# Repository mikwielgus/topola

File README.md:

<!--
SPDX-FileCopyrightText: 2024 Topola contributors

SPDX-License-Identifier: MIT
-->

# Topola

[Topola](https://topola.dev) is a work-in-progress interactive
topological router for printed circuit boards (PCBs) in Rust.

## Chat

Join the official [Matrix
chatroom](https://matrix.to/#/%23topola:tchncs.de) or [IRC
channel](https://webchat.oftc.net/?channels=#topola) to talk with the
developers. Both chatrooms are bridged, so it does not matter which one
you join.

## Installation

To install Topola, follow our [Installation guide](INSTALL.md).

## Contributing

*Anyone* can contribute to Topola, including you. If you want to help us out,
follow our [Contribution guide](CONTRIBUTING.md).

The easiest way to contribute is by reporting issues on our
[issue tracker](https://codeberg.org/topola/topola/issues). If you know any
language other than English, you can help by translating Topola on
[Codeberg's Weblate](https://translate.codeberg.org/engage/topola/).

Our official repository is on
[Codeberg](https://codeberg.org/topola/topola). We also have a mirror
repository on [GitHub](https://github.com/mikwielgus/topola).

## Licence

Topola is licensed under the [MIT licence](LICENSES/MIT.txt). Files present in
the `assets/` directory are dual-licensed as under MIT or
[Creative Commons Attribution 4.0 International](LICENSES/CC-BY-4.0.txt)
licence. The file `crates/planar-incr-embed/src/math.rs` is dual-licensed as under
MIT or [Apache 2.0](LICENSES/Apache-2.0.txt) licence.

### Inbound licence is outbound licence

Unless you explicitly state otherwise, any contribution intentionally submitted
for inclusion in the work by you will be licensed as described above, without
any additional terms or conditions.

## Acknowledgements

This project is funded through the NGI0 Entrust Fund, a fund established by
NLnet with financial support from the European Commission's Next Generation
Internet programme, under the aegis of DG Communications Networks, Content and
Technology under grant agreement No 101069594.

## Gallery

![Screenshot of a PCB layout of an IR remote with a 3x4 tactswitch keyboard,
displayed in KiCad.](./assets/screenshots/3x4_tactswitch_ir_remote.png "3x4 tactswitch IR remote PCB layout in KiCad")

![Screenshot of a PCB layout of a THT DB-25 to THT DB-25 gender changer adapter
board, displayed in KiCad](./assets/screenshots/tht_db25_to_tht_db25.png "THT DB-25 to THT DB-25 gender changer adapter PCB layout in KiCad")

![Screenshot of a PCB layout of a 4x4 1206 LED matrix breakout board, displayed
in KiCad](./assets/screenshots/4x4_1206_led_matrix_breakout.png "4x4 1206 LED matrix breakout PCB layout in KiCad")

![Animation. There is a rubber band-like trace following cursor,
navigating a very simple maze. The maze and the trace are red, the
background is solid black but also very slightly white and dark
blue.](./assets/screencasts/pre-egui_interactive_routing.gif "Interactive routing")

![Animation showing a trace, behaving like a rubber band, routed around
obstacles step by step. Attempted alternative paths and a guiding mesh
are shown.](./assets/screencasts/pre-egui_debug_visualization.gif "Debug visualization")

![Animation. There are two upward barriers, with some space between tem,
around which four rubberband traces, one over another, are wrapped.
Enter mouse cursor. The cursor begins to stretch the left barrier to the
right. As it's stretched, the traces cease to be wrapped around the
right barrier, becoming "free". The traces and the barrier are
two-dimensional and all solid red. The background is black but also very
slightly white and blue.](./assets/screencasts/pre-egui_unwrapping_bends.gif "Unwrapping bends")

![This animation shows four traces wrapped around a vertical barrier
like rubberbands. Computer cursor appears and starts dragging the
barrier's top end left and right, up and down, elastically stretching
the barrier and having the traces continue being wrapped on the barrier
regardless of its position. The traces and the barrier are all solid
red. The background is black but also very slightly white and
blue.](./assets/screencasts/pre-egui_dragging_with_bends.gif "Dragging with bends")

![Animation. There is an upward barrier in the middle and dots on the
left and right of it, four each. A trace is drawn from the leftmost dot
on the left to the rightmost dot on the right. Then a trace is drawn
from the second leftmost dot on the left to the second rightmost dot on
the right, displacing the previous trace so that there's space for the
new one. Same happens for the remaining dots. The dots, traces and
barrier are all solid red. The background is black but also very
slightly white and blue.](./assets/screencasts/pre-egui_squeezing_through_under_bends.gif "Squeezing through under bends")

![Animation showing three red-colored traces pass around a barrier.
Trace bends are not aligned to a grid unlike most PCB layouts these days
(this is called "topological routing"). The traces and the barrier are
all solid red. The background is black but also very slightly white and
blue.](./assets/screenshots/pre-egui_stacked_bends.png "Stacking bends")

![Animation showing a trace zigzagging around two barriers. The trace
and the barriers are all solid red. The background is black but also
very slightly white and blue.](./assets/screenshots/pre-egui_zigzag.png "Zigzag")

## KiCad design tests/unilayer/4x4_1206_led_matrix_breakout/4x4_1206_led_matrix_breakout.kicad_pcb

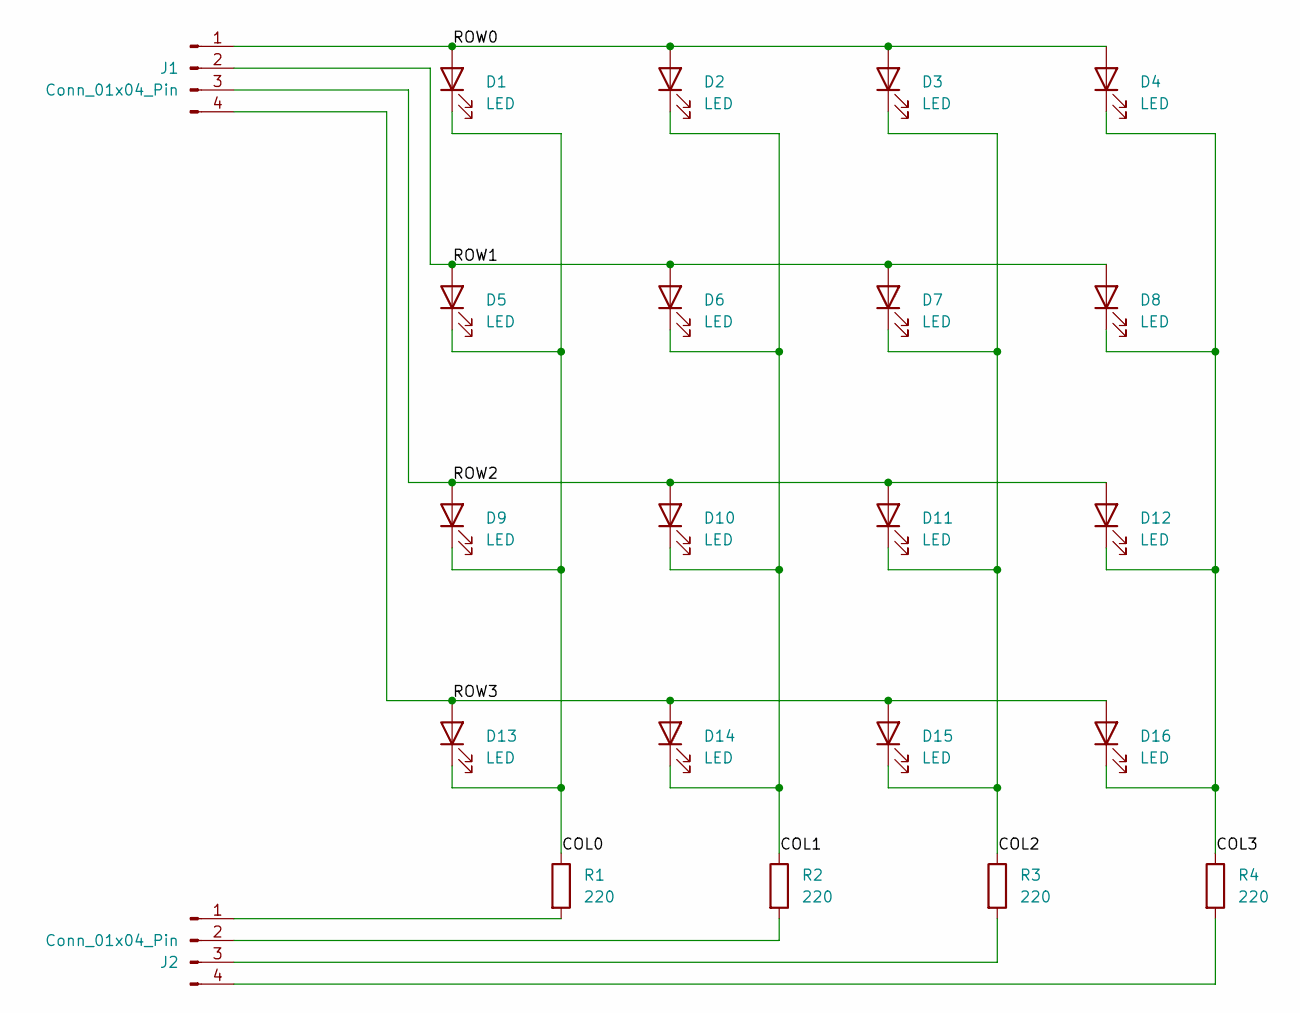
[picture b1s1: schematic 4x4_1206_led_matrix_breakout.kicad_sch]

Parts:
D1, D2, D3, D4, D5, D6, D7, D8, D9, D10, D11, D12, D13, D14, D15, D16: LED; LED_1206_3216Metric
J1, J2: Conn_01x04_Pin; PinHeader_1x04_P2.54mm_Horizontal
R1, R2, R3, R4: 220; R_0603_1608Metric

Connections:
/COL0: D1.1 (K), D5.1 (K), D9.1 (K), D13.1 (K), R1.1
/COL1: D2.1 (K), D6.1 (K), D10.1 (K), D14.1 (K), R2.1
/COL2: D3.1 (K), D7.1 (K), D11.1 (K), D15.1 (K), R3.1
/COL3: D4.1 (K), D8.1 (K), D12.1 (K), D16.1 (K), R4.1
/ROW0: D1.2 (A), D2.2 (A), D3.2 (A), D4.2 (A), J1.1
/ROW1: D5.2 (A), D6.2 (A), D7.2 (A), D8.2 (A), J1.2
/ROW2: D9.2 (A), D10.2 (A), D11.2 (A), D12.2 (A), J1.3
/ROW3: D13.2 (A), D14.2 (A), D15.2 (A), D16.2 (A), J1.4
unnamed: J2.1, R1.2
unnamed: J2.2, R2.2
unnamed: J2.3, R3.2
unnamed: J2.4, R4.2

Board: 2 copper layers, 22 parts (2 on the bottom side), 12 nets, no tracks yet.

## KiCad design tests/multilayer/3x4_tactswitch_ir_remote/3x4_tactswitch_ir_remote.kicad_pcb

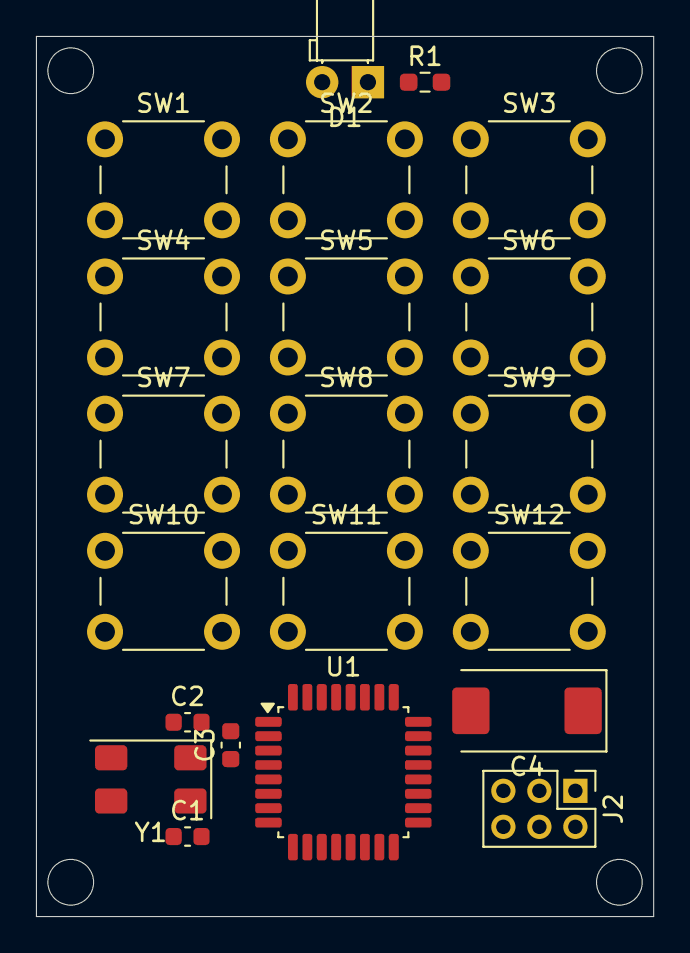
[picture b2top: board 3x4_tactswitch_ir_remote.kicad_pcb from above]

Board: 2 copper layers, 34.3 x 48.9 mm, 21 parts (0 on the bottom side), 17 nets, no tracks yet.

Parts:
C1, C2: 22p; C_0603_1608Metric
C3: 100n; C_0603_1608Metric
C4: 470u; CP_EIA-7343-31_Kemet-D
D1: IR204A; LED_D3.0mm_Horizontal_O1.27mm_Z2.0mm_IRBlack
J2: Conn_01x06_Pin; PinHeader_2x03_P2.00mm_Vertical
R1: 220; R_0603_1608Metric_Pad0.98x0.95mm_HandSolder
SW1, SW2, SW3, SW4, SW5, SW6, SW7, SW8, SW9, SW10, SW11, SW12: SW_Push; SW_PUSH_6mm
U1: ATmega328P-AU; TQFP-32_7x7mm_P0.8mm
Y1: Crystal_GND23; Crystal_SMD_0603-4Pin_6.0x3.5mm

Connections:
+5V: C3.1, C4.1, J2.1, U1.4 (VCC), U1.6 (VCC), U1.18 (AVCC), U1.20 (AREF)
/COL0: SW1.2, SW4.2, SW7.2, SW10.2, U1.12 (PB0)
/COL1: SW2.2, SW5.2, SW8.2, SW11.2, U1.13 (PB1)
/COL2: SW3.2, SW6.2, SW9.2, SW12.2, U1.14 (PB2)
/MISO: J2.4, U1.16 (PB4)
/MOSI: J2.3, U1.15 (PB3)
/RESET: J2.2, U1.29 (~RESET/PC6)
/ROW0: SW1.1, SW2.1, SW3.1, U1.23 (PC0)
/ROW1: SW4.1, SW5.1, SW6.1, U1.24 (PC1)
/ROW2: SW7.1, SW8.1, SW9.1, U1.25 (PC2)
/ROW3: SW10.1, SW11.1, SW12.1, U1.26 (PC3)
/SCK: J2.5, U1.17 (PB5)
GND: C1.1, C2.1, C3.2, C4.2, J2.6, R1.2, U1.3 (GND), U1.5 (GND), U1.21 (GND), Y1.2, Y1.3
unnamed: D1.2 (A), U1.30 (PD0)
unnamed: D1.1 (K), R1.1
unnamed: C2.2, U1.7 (XTAL1/PB6), Y1.1
unnamed: C1.2, U1.8 (XTAL2/PB7), Y1.4

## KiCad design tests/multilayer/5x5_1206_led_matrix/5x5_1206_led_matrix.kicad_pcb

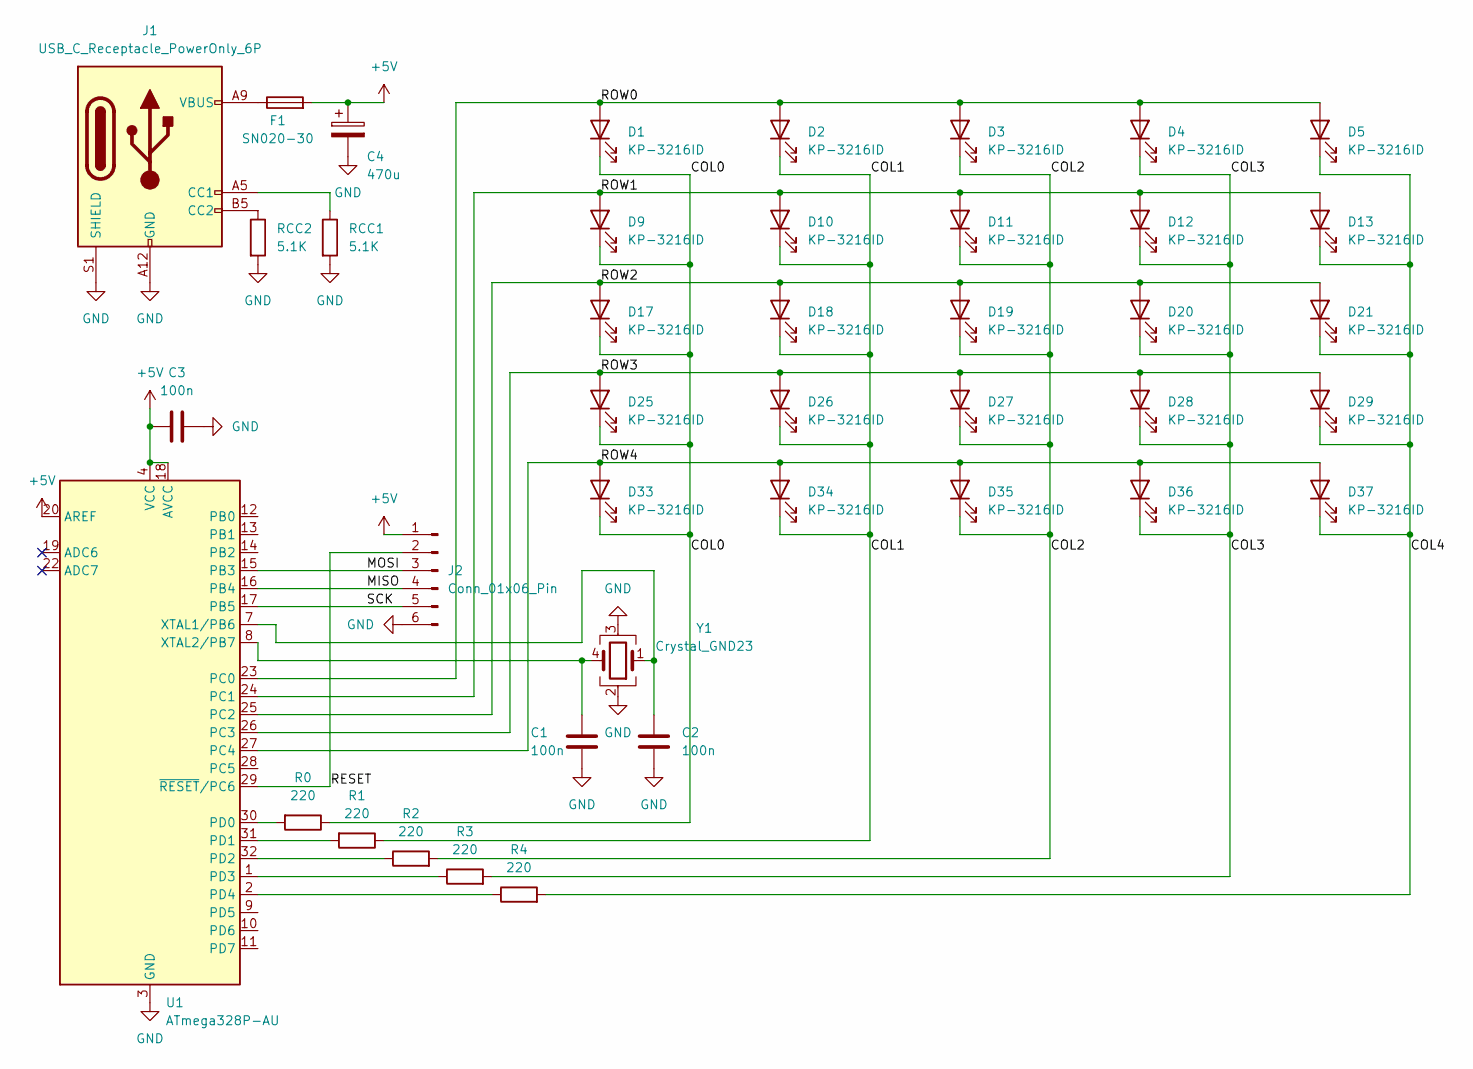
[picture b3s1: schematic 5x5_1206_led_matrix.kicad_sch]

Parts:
C1, C2, C3: 100n; C_0603_1608Metric
C4: 470u; CP_EIA-7343-31_Kemet-D
D1, D2, D3, D4, D5, D9, D10, D11, D12, D13, D17, D18, D19, D20, D21, D25, D26, D27, D28, D29, D33, D34, D35, D36, D37: KP-3216ID; LED_1206_3216Metric
F1: SN020-30; Fuse_1206_3216Metric
J1: USB_C_Receptacle_PowerOnly_6P; USB_C_Receptacle_GCT_USB4125-xx-x-0190_6P_TopMnt_Horizontal
J2: Conn_01x06_Pin; PinHeader_2x03_P2.00mm_Vertical
R0, R1, R2, R3, R4: 220; R_0603_1608Metric
RCC1, RCC2: 5.1K; R_0603_1608Metric
U1: ATmega328P-AU; TQFP-32_7x7mm_P0.8mm
Y1: Crystal_GND23; Crystal_SMD_0603-4Pin_6.0x3.5mm

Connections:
+5V: C3.1, C4.1, F1.2, J2.1, U1.4 (VCC), U1.6 (VCC), U1.18 (AVCC), U1.20 (AREF)
/COL0: D1.1 (K), D9.1 (K), D17.1 (K), D25.1 (K), D33.1 (K), R0.1
/COL1: D2.1 (K), D10.1 (K), D18.1 (K), D26.1 (K), D34.1 (K), R1.1
/COL2: D3.1 (K), D11.1 (K), D19.1 (K), D27.1 (K), D35.1 (K), R2.2
/COL3: D4.1 (K), D12.1 (K), D20.1 (K), D28.1 (K), D36.1 (K), R3.2
/COL4: D5.1 (K), D13.1 (K), D21.1 (K), D29.1 (K), D37.1 (K), R4.2
/MISO: J2.4, U1.16 (PB4)
/MOSI: J2.3, U1.15 (PB3)
/RESET: J2.2, U1.29 (~RESET/PC6)
/ROW0: D1.2 (A), D2.2 (A), D3.2 (A), D4.2 (A), D5.2 (A), U1.23 (PC0)
/ROW1: D9.2 (A), D10.2 (A), D11.2 (A), D12.2 (A), D13.2 (A), U1.24 (PC1)
/ROW2: D17.2 (A), D18.2 (A), D19.2 (A), D20.2 (A), D21.2 (A), U1.25 (PC2)
/ROW3: D25.2 (A), D26.2 (A), D27.2 (A), D28.2 (A), D29.2 (A), U1.26 (PC3)
/ROW4: D33.2 (A), D34.2 (A), D35.2 (A), D36.2 (A), D37.2 (A), U1.27 (PC4)
/SCK: J2.5, U1.17 (PB5)
GND: C1.1, C2.1, C3.2, C4.2, J1.A12 (GND), J1.B12 (GND), J1.S1 (SHIELD), J2.6, RCC1.2, RCC2.2, U1.3 (GND), U1.5 (GND), U1.21 (GND), U1.33 (GND), Y1.2, Y1.3
unnamed: F1.1, J1.A9 (VBUS), J1.B9 (VBUS)
unnamed: J1.A5 (CC1), RCC1.1
unnamed: J1.B5 (CC2), RCC2.1
unnamed: R0.2, U1.30 (PD0)
unnamed: R1.2, U1.31 (PD1)
unnamed: R2.1, U1.32 (PD2)
unnamed: R3.1, U1.1 (PD3)
unnamed: R4.1, U1.2 (PD4)
unnamed: C2.2, U1.7 (XTAL1/PB6), Y1.1
unnamed: C1.2, U1.8 (XTAL2/PB7), Y1.4

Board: 2 copper layers, 41 parts (16 on the bottom side), 26 nets, no tracks yet.

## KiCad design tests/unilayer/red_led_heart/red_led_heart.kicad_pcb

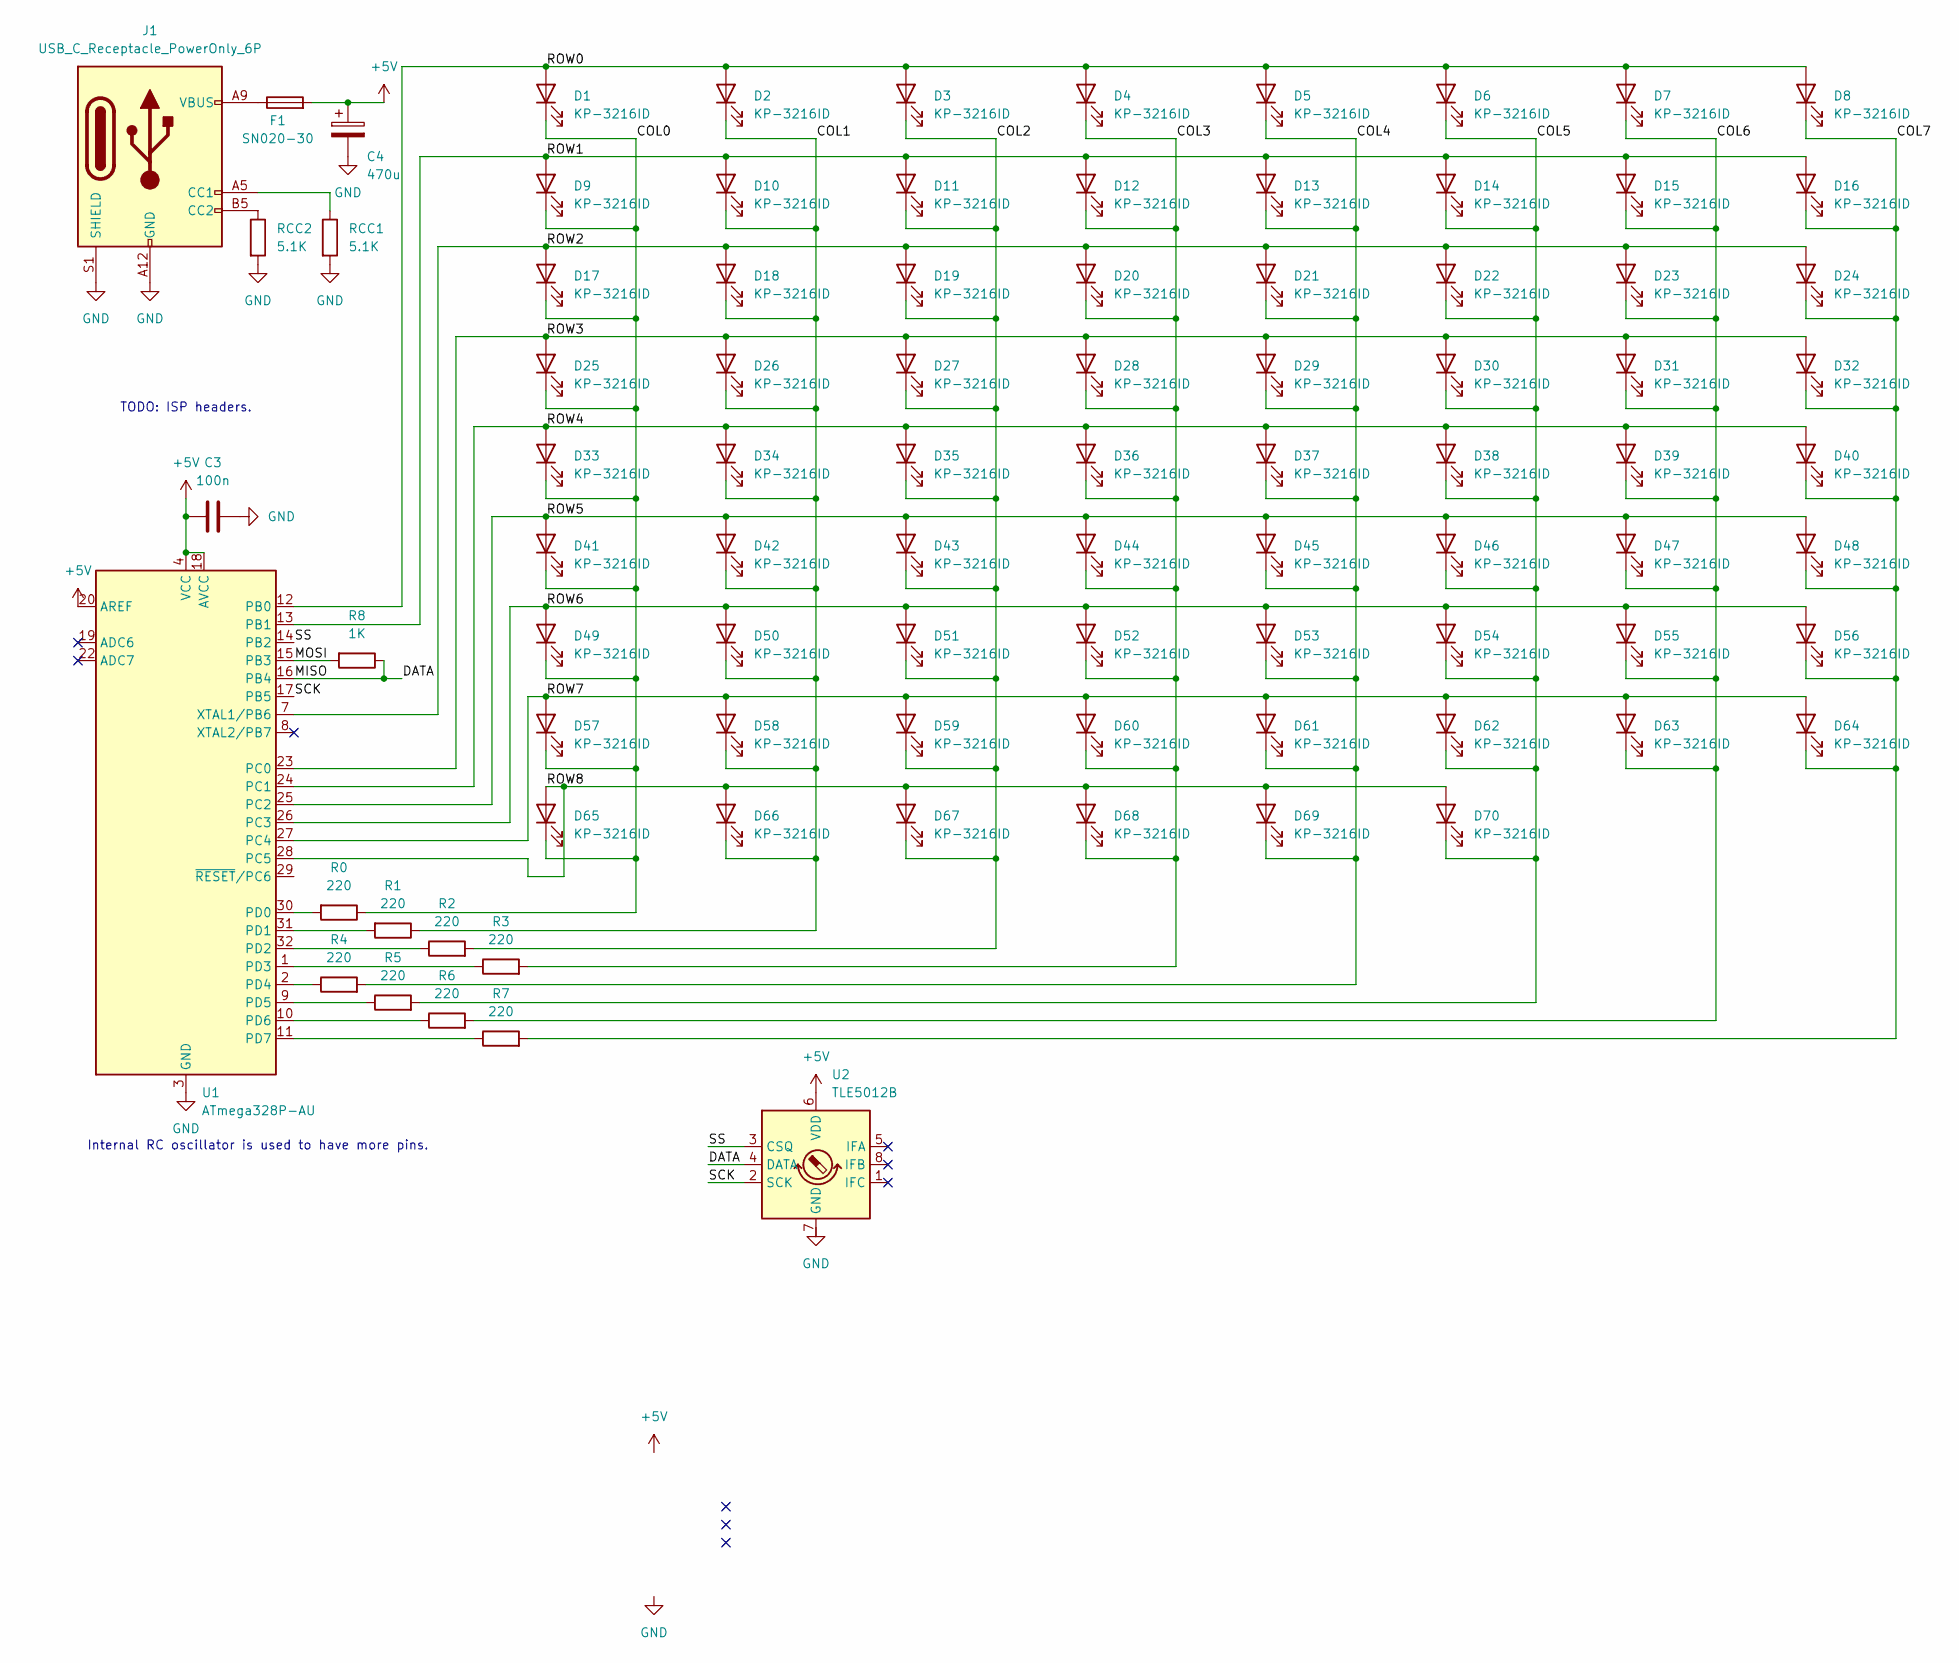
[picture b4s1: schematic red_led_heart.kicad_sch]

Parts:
C3: 100n; C_0603_1608Metric
C4: 470u; CP_EIA-7343-31_Kemet-D
D1, D2, D3, D4, D5, D6, D7, D8, D9, D10, D11, D12, D13, D14, D15, D16, D17, D18, D19, D20, D21, D22, D23, D24, D25, D26, D27, D28, D29, D30, D31, D32, D33, D34, D35, D36, D37, D38, D39, D40, D41, D42, D43, D44, D45, D46, D47, D48, D49, D50, D51, D52, D53, D54, D55, D56, D57, D58, D59, D60, D61, D62, D63, D64, D65, D66, D67, D68, D69, D70: KP-3216ID; LED_1206_3216Metric
F1: SN020-30; Fuse_1206_3216Metric
J1: USB_C_Receptacle_PowerOnly_6P; USB_C_Receptacle_GCT_USB4125-xx-x-0190_6P_TopMnt_Horizontal
R0, R1, R2, R3, R4, R5, R6, R7: 220; R_0603_1608Metric
R8: 1K; R_0603_1608Metric
RCC1, RCC2: 5.1K; R_0603_1608Metric
U1: ATmega328P-AU; TQFP-32_7x7mm_P0.8mm
U2: TLE5012B; SOIC-8_3.9x4.9mm_P1.27mm

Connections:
+5V: C3.1, C4.1, F1.2, U1.4 (VCC), U1.6 (VCC), U1.18 (AVCC), U1.20 (AREF), U2.6 (VDD)
/COL0: D1.1 (K), D9.1 (K), D17.1 (K), D25.1 (K), D33.1 (K), D41.1 (K), D49.1 (K), D57.1 (K), D65.1 (K), R0.1
/COL1: D2.1 (K), D10.1 (K), D18.1 (K), D26.1 (K), D34.1 (K), D42.1 (K), D50.1 (K), D58.1 (K), D66.1 (K), R1.1
/COL2: D3.1 (K), D11.1 (K), D19.1 (K), D27.1 (K), D35.1 (K), D43.1 (K), D51.1 (K), D59.1 (K), D67.1 (K), R2.2
/COL3: D4.1 (K), D12.1 (K), D20.1 (K), D28.1 (K), D36.1 (K), D44.1 (K), D52.1 (K), D60.1 (K), D68.1 (K), R3.2
/COL4: D5.1 (K), D13.1 (K), D21.1 (K), D29.1 (K), D37.1 (K), D45.1 (K), D53.1 (K), D61.1 (K), D69.1 (K), R4.2
/COL5: D6.1 (K), D14.1 (K), D22.1 (K), D30.1 (K), D38.1 (K), D46.1 (K), D54.1 (K), D62.1 (K), D70.1 (K), R5.2
/COL6: D7.1 (K), D15.1 (K), D23.1 (K), D31.1 (K), D39.1 (K), D47.1 (K), D55.1 (K), D63.1 (K), R6.2
/COL7: D8.1 (K), D16.1 (K), D24.1 (K), D32.1 (K), D40.1 (K), D48.1 (K), D56.1 (K), D64.1 (K), R7.2
/DATA: R8.1, U1.16 (PB4), U2.4 (DATA)
/MOSI: R8.2, U1.15 (PB3)
/ROW0: D1.2 (A), D2.2 (A), D3.2 (A), D4.2 (A), D5.2 (A), D6.2 (A), D7.2 (A), D8.2 (A), U1.12 (PB0)
/ROW1: D9.2 (A), D10.2 (A), D11.2 (A), D12.2 (A), D13.2 (A), D14.2 (A), D15.2 (A), D16.2 (A), U1.13 (PB1)
/ROW2: D17.2 (A), D18.2 (A), D19.2 (A), D20.2 (A), D21.2 (A), D22.2 (A), D23.2 (A), D24.2 (A), U1.7 (XTAL1/PB6)
/ROW3: D25.2 (A), D26.2 (A), D27.2 (A), D28.2 (A), D29.2 (A), D30.2 (A), D31.2 (A), D32.2 (A), U1.23 (PC0)
/ROW4: D33.2 (A), D34.2 (A), D35.2 (A), D36.2 (A), D37.2 (A), D38.2 (A), D39.2 (A), D40.2 (A), U1.24 (PC1)
/ROW5: D41.2 (A), D42.2 (A), D43.2 (A), D44.2 (A), D45.2 (A), D46.2 (A), D47.2 (A), D48.2 (A), U1.25 (PC2)
/ROW6: D49.2 (A), D50.2 (A), D51.2 (A), D52.2 (A), D53.2 (A), D54.2 (A), D55.2 (A), D56.2 (A), U1.26 (PC3)
/ROW7: D57.2 (A), D58.2 (A), D59.2 (A), D60.2 (A), D61.2 (A), D62.2 (A), D63.2 (A), D64.2 (A), U1.27 (PC4)
/ROW8: D65.2 (A), D66.2 (A), D67.2 (A), D68.2 (A), D69.2 (A), D70.2 (A), U1.28 (PC5)
/SCK: U1.17 (PB5), U2.2 (SCK)
/SS: U1.14 (PB2), U2.3 (CSQ)
GND: C3.2, C4.2, J1.A12 (GND), J1.B12 (GND), J1.S1 (SHIELD), RCC1.2, RCC2.2, U1.3 (GND), U1.5 (GND), U1.21 (GND), U1.33 (GND)
unnamed: F1.1, J1.A9 (VBUS), J1.B9 (VBUS)
unnamed: J1.A5 (CC1), RCC1.1
unnamed: J1.B5 (CC2), RCC2.1
unnamed: R0.2, U1.30 (PD0)
unnamed: R1.2, U1.31 (PD1)
unnamed: R2.1, U1.32 (PD2)
unnamed: R3.1, U1.1 (PD3)
unnamed: R4.1, U1.2 (PD4)
unnamed: R5.1, U1.9 (PD5)
unnamed: R6.1, U1.10 (PD6)
unnamed: R7.1, U1.11 (PD7)

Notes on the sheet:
Internal RC oscillator is used to have more pins.
TODO: ISP headers.

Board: 2 copper layers, 87 parts (17 on the bottom side), 34 nets, no tracks yet.

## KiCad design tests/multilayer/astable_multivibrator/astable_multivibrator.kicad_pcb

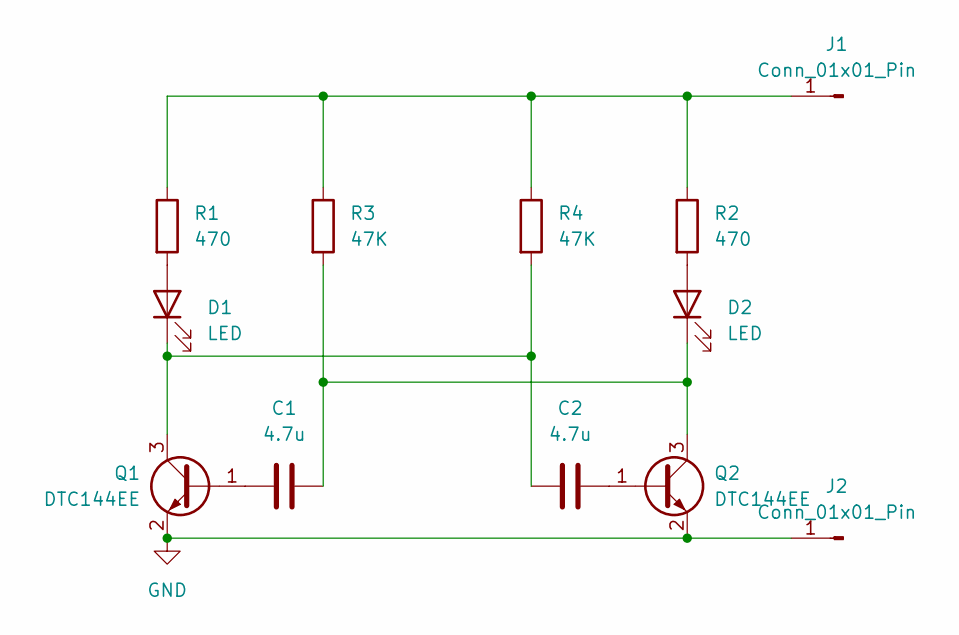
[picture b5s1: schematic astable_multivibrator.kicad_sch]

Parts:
C1, C2: 4.7u; C_0201_0603Metric
D1, D2: LED; LED_1206_3216Metric
J1, J2: Conn_01x01_Pin; SolderWire-0.1sqmm_1x01_D0.4mm_OD1mm
Q1, Q2: DTC144EE; SOT-523
R1, R2: 470; R_0201_0603Metric
R3, R4: 47K; R_0201_0603Metric

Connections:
GND: J2.1, Q1.2 (E), Q2.2 (E)
unnamed: D1.2 (A), R1.2
unnamed: C2.1, D1.1 (K), Q1.3 (C), R4.2
unnamed: D2.2 (A), R2.2
unnamed: C1.2, D2.1 (K), Q2.3 (C), R3.2
unnamed: J1.1, R1.1, R2.1, R3.1, R4.1
unnamed: C1.1, Q1.1 (B)
unnamed: C2.2, Q2.1 (B)

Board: 2 copper layers, 12 parts (10 on the bottom side), 8 nets, no tracks yet.

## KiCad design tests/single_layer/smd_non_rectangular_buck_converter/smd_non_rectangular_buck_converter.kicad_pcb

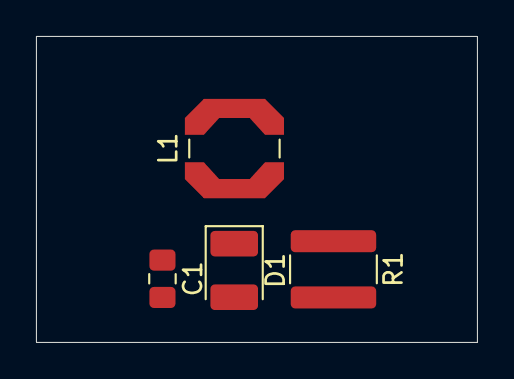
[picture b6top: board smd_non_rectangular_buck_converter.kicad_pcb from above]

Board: 2 copper layers, 24.5 x 17.0 mm, 4 parts (0 on the bottom side), 3 nets, no tracks yet.

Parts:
C1: C; C_0805_2012Metric_Pad1.18x1.45mm_HandSolder
D1: D; D_1210_3225Metric_Pad1.42x2.65mm_HandSolder
L1: L; L_Coilcraft_LPS5030
R1: R; R_1218_3246Metric_Pad1.22x4.75mm_HandSolder

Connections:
+3.3V: C1.1, L1.2, R1.1
GND: C1.2, D1.2 (A), R1.2
unnamed: D1.1 (K), L1.1

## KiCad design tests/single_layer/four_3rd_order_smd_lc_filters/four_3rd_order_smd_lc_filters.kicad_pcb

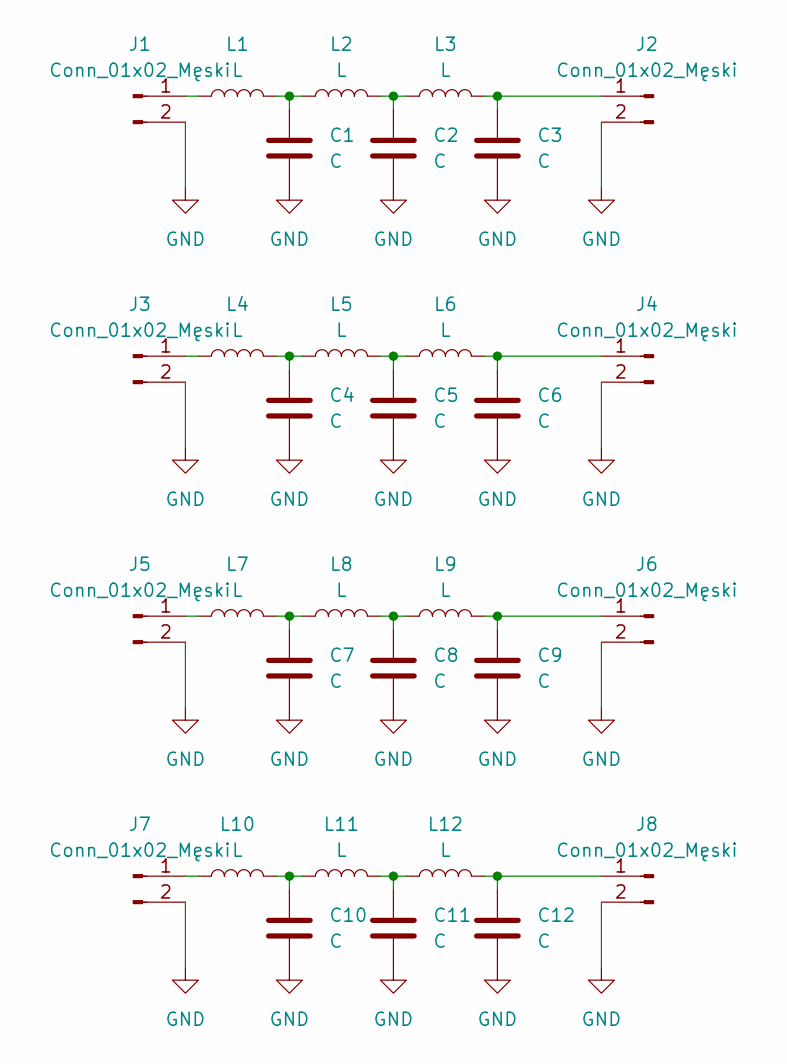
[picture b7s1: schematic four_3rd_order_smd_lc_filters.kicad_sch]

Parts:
C1, C2, C3, C4, C5, C6, C7, C8, C9, C10, C11, C12: C; C_0603_1608Metric_Pad1.08x0.95mm_HandSolder
J1, J2, J3, J4, J5, J6, J7, J8: Conn_01x02_Męski; PinHeader_1x02_P1.00mm_Horizontal
L1, L2, L3, L4, L5, L6, L7, L8, L9, L10, L11, L12: L; L_0603_1608Metric_Pad1.05x0.95mm_HandSolder

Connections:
GND: C1.2, C2.2, C3.2, C4.2, C5.2, C6.2, C7.2, C8.2, C9.2, C10.2, C11.2, C12.2, J1.2, J2.2, J3.2, J4.2, J5.2, J6.2, J7.2, J8.2
unnamed: C1.1, L1.2, L2.1
unnamed: C2.1, L2.2, L3.1
unnamed: C4.1, L4.2, L5.1
unnamed: C5.1, L5.2, L6.1
unnamed: C7.1, L7.2, L8.1
unnamed: C8.1, L8.2, L9.1
unnamed: C10.1, L10.2, L11.1
unnamed: C11.1, L11.2, L12.1
unnamed: J1.1, L1.1
unnamed: C3.1, J2.1, L3.2
unnamed: J3.1, L4.1
unnamed: C6.1, J4.1, L6.2
unnamed: J5.1, L7.1
unnamed: C9.1, J6.1, L9.2
unnamed: J7.1, L10.1
unnamed: C12.1, J8.1, L12.2

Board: 2 copper layers, 32 parts (8 on the bottom side), 17 nets, no tracks yet.

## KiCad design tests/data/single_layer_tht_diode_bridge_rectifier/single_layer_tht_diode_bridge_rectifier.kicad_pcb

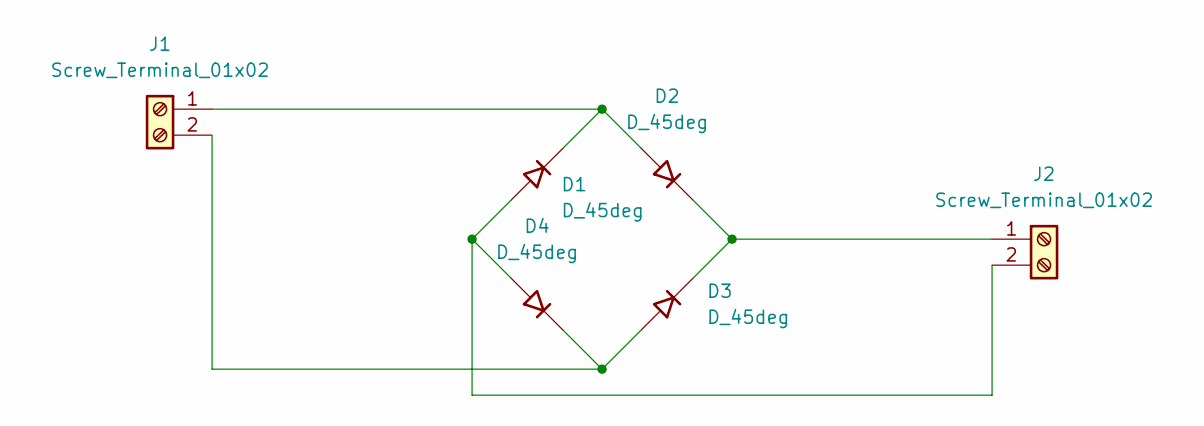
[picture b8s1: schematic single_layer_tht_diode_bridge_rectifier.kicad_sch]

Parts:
D1, D2, D3, D4: D_45deg; D_DO-15_P10.16mm_Horizontal
J1, J2: Screw_Terminal_01x02; TerminalBlock_bornier-2_P5.08mm

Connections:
unnamed: D1.2 (A), D4.2 (A), J2.2
unnamed: D1.1 (K), D2.2 (A), J1.1
unnamed: D2.1 (K), D3.1 (K), J2.1
unnamed: D3.2 (A), D4.1 (K), J1.2

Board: 2 copper layers, 6 parts (0 on the bottom side), 4 nets, no tracks yet.

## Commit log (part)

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2025-07-09 refactor(router/navmesh): Split out navmesh triangulation into "prenavmesh" module
2025-07-10 feat(autorouter/autoroute): Track progress of also past and future ratlines
2025-07-14 refactor(autorouter/ratsnest): Split out ratline code to new file, ratline.rs
2025-07-15 refactor(topola-egui): Split out some display code to new file, displayer.rs
2025-07-16 fix(geometry/recording_with_rtree): Attach bends applied from edit
    This was unimplemented, which made both redo and cane removal not work
    correctly.
2025-07-17 fix(drawing/drawing): Remove temporary recorder in outward bow updating code
    I'm skeptical if this actually works, and I see no difference with this
    removed. If this breaks the topo-navmesh code, it may be a better option
    to just disable squeezing through under bends in it.
2025-07-17 refactor(drawing/drawing): Some minor changes to method naming, comments, contracts
2025-07-17 fix(geometry/with_rtree): Do not remove only-modified dots when applying edit
    This fixes a panic when undoing some bands.
    180952c94f1c7c56c2ce5d2bdd3ab672aa0ccfec did not fix this problem
    because we did not stop removing modified dots.
2025-07-17 feat(autorouter/autoroute): Record band assigns so undo actually works
    Aborting the autoroute stepper was unimplemented and it would make the
    autorouting job finish instead. This is fixed now.
2025-07-19 test: Test tht_de9_to_tht_de9 with permuted autorouting as well
2025-07-23 Translated using Weblate (Chinese (Simplified Han script))
    Currently translated at 100.0% (61 of 61 strings)
    Translation: Topola/Topola
    Translate-URL: https://translate.codeberg.org/projects/topola/topola/zh_Hans/
2025-08-09 feat(geometry/geometry): Create outward bend walker, use it for R-tree updates
    Drawing and above abstraction layers do not use it yet, but this will
    change soon.
2025-08-10 refactor(autorouter/autoroute): Store vecs of edits instead of large edits
    This results in a large copy, but it should be possible to refactor the
    code later to get rid of this.
2025-08-12 fix(drawing/drawing): Don't infringe on and from loose dots
    These resulted in false positives for line-of-sight paths.
2025-08-15 refactor(drawing/guide): Make method names somewhat clearer
2025-08-19 test: Add vga_dac_breakout test
    This simple breakout board tests routing around SMD pads.
2025-08-19 Translated using Weblate (Chinese (Simplified Han script))
    Currently translated at 100.0% (63 of 63 strings)
    Translation: Topola/Topola
    Translate-URL: https://translate.codeberg.org/projects/topola/topola/zh_Hans/
2025-08-23 refactor(router/thetastar): Backtrack not once, but repeatedly, if condition is met
2025-08-24 refactor(drawing/query): Rename collect.rs to query.rs, change trait to direct impl
2025-08-28 fix(router/navmesh): Make sure all clearance-intersecting navnodes have the same edges
    This does not yet fully fix the problem with routing around SMD pads
    failing, but is a step forward.
2025-08-30 refactor(specctra/design): Place fillet circles, netless for now
2025-09-01 refactor(autorouter/autoroute): Move permuting to new trait
2025-09-02 refactor(drawing/drawing): Add filtering predicate also for `.insert_cane(...)`
2025-09-04 fix(autorouter/ratline): Don't count ratlines with shared endpoint as intersecting
2025-09-05 refactor(autorouter/autorouter): Move ratline sorting to `permutator.rs`
2025-09-09 feat(autorouter/permuter): Implement permutation by ratline cut
    Not yet used, and can get stuck in an infinite loop, but the cut seems
    to work.
2025-09-15 chore: Attempt to fix missing `cargo binstall` command error in CI
2025-09-15 refactor(geometry/geometry): Replace `NodeIndex<usize>` with just `usize`
    This is a step towards ceasing to use Petgraph as internal storage for
    geometry.
2025-09-15 refactor(graph): Rename `GetPetgraphIndex` to `GetIndex`
2025-09-17 test: Split test_tht_de9_to_tht_de9 into two test routines to measure speed better
2025-09-17 test: Add test routines for `4x4_1206_led_matrix_breakout`
2025-09-17 chore: Set build profile correctly this time in CI
2025-09-17 fix(geometry/geometry): Rewrite uses of `debug_assert!(...)` to not break release
2025-09-21 feat(topola-egui): Highlight node index of the obstacling primitive
2025-09-22 feat(topola-egui): Hide ratlines that were already routed
2025-09-23 fix(autorouter/ratsnest): Prioritize principal layer ratlines over others
2025-09-25 feat(autorouter/presorter): Make presorter parametrizable
2025-09-27 Translated using Weblate (Chinese (Simplified Han script))
    Currently translated at 100.0% (64 of 64 strings)
    Translation: Topola/Topola
    Translate-URL: https://translate.codeberg.org/projects/topola/topola/zh_Hans/
2025-09-30 refactor(autorouter/anterouter): Anchor in reference to dot circle, not bbox
2025-10-02 feat(autorouter/compass_direction): Anteroute fanout vias in eight "compass" directions
2025-10-03 feat(autorouter/anterouter): Anteroute fanout segs to fanout vias
2025-10-03 Translated using Weblate (Chinese (Simplified Han script))
    Currently translated at 100.0% (65 of 65 strings)
    Translation: Topola/Topola
    Translate-URL: https://translate.codeberg.org/projects/topola/topola/zh_Hans/
2025-10-07 fix(autorouter/compass_direction): Correct flipped North/South
2025-10-08 fix(autorouter/anterouter): Correctly calculate fanout lengths
2025-10-12 refactor(autorouter/autorouter): Put ratsnest in wrapper, mostly transparent for now
2025-10-14 Translated using Weblate (Chinese (Simplified Han script))
    Currently translated at 100.0% (66 of 66 strings)
    Translation: Topola/Topola
    Translate-URL: https://translate.codeberg.org/projects/topola/topola/zh_Hans/
2025-10-16 fix(autorouter/anterouter): Make anterouting undo-redoable
2025-10-17 fix(autorouter/anterouter): Don't fan out if ratline is on same layer
2025-10-18 refactor(stepper): Have reconfigure configuration take any type, not only `Vec<_>`
2025-10-19 fix(autorouter/conncomps): Take into account vias when computing connected components
2025-10-20 refactor(specctra-core): Remove `layer_count` from `SpecctraMesadata`
    This information is already stored in `Drawing`, I somehow missed that
    when I was adding this field.
2025-10-21 feat(autorouter/autorouter): Impl. rudimentary multilayer reconfigurator (not yet functional)
2025-10-22 refactor(autorouter/planar_autoroute): Wrap ratline vec in new "configuration" struct
    This will be useful later.
2025-10-23 test: Don't use `.terminating_dots(...)`, as it won't be accessible since next commit
2025-10-24 refactor(autorouter/ratline): Don't store `layer` in ratlines
    Translayer ratlines exist, so it makes no sense to assign them a layer.
2025-10-25 fix(autorouter/anterouter): Remove via from terminating dot map if fanout seg creation fails
2025-10-27 refactor(autorouter/multilayer_reconfigurer): Move multilayer reconfiguration trigger code
2025-10-28 fix(autorouter/multilayer_preconfigurer): Make ratline endpoint terminating dot on routed layer
2025-10-29 feat(topola-egui): Move debug-only view options to new menubar's menu "Debug"
2025-10-30 Translated using Weblate (German)
    Currently translated at 100.0% (68 of 68 strings)
    Translation: Topola/Topola
    Translate-URL: https://translate.codeberg.org/projects/topola/topola/de/
2025-10-30 Update translation files
    Updated by "Cleanup translation files" add-on in Weblate.
    Translation: Topola/Topola
    Translate-URL: https://translate.codeberg.org/projects/topola/topola/
2025-10-31 docs: Change one more nitpick in readme
2025-11-03 feat(topola-egui): Make step rate slider go up to 1000 steps/s
2025-11-04 feat(autorouter/multilayer_reconfigurator): Use our new trigger mechanism for reconfiguration
2025-11-04 feat(stepper): Replace overengineered SMA rate timeout with two accumulators
2025-11-05 fix(topola-cli): Fix CLI build broken since 8216d3a907
2025-11-05 Translated using Weblate (Chinese (Simplified Han script))
    Currently translated at 100.0% (70 of 70 strings)
    Translation: Topola/Topola
    Translate-URL: https://translate.codeberg.org/projects/topola/topola/zh_Hans/
2025-11-07 Translated using Weblate (German)
    Currently translated at 93.0% (67 of 72 strings)
    Translation: Topola/Topola
    Translate-URL: https://translate.codeberg.org/projects/topola/topola/de/
2025-11-09 Translated using Weblate (German)
    Currently translated at 97.2% (70 of 72 strings)
    Translation: Topola/Topola
    Translate-URL: https://translate.codeberg.org/projects/topola/topola/de/
2025-11-16 feat(router/navmesh): Reduce number of navedges
    This provides a speedup, but may break squeezing through under bends in
    some corner cases.
2025-11-17 test: Add multilayer 5x5 1206 LED matrix test project, without testing routine for now
2025-11-18 feat(autorouter/planar_reconfigurer): Make g-scores proportional to number of changed routes
2025-11-21 refactor(autorouter/planar_autoroute): Slightly reduce code duplication
2025-11-24 chore: Add screenshot of 3x4_tactswitch_ir_remote to gallery
2025-11-25 chore: Add screenshot of autorouted 4x4_1206_matrix_breakout to gallery, with some small changes
2025-11-25 chore: Commit forgotten changes to readme
2025-11-29 feat(topola-egui): Display origin-destination by default
2025-12-01 fix(router/navmesh): Add (failed) attempt to prune some navedges
    This did not achieve the intended goal, but I'm committing it anyway
    just to have it in history.
2026-03-03 Fix issue #293
2026-03-09 feat(topola-egui): Display loaded board's boundary
2026-03-09 feat(topola): Add navmesher to maintain navmeshes
2026-03-10 feat(topola/specctra): Insert and display rectangular pins
2026-03-10 Import and display segments in pads
2026-03-11 Flip components if flipped in Specctra DSN
2026-03-11 Wrap `Board` in `NavmesherBoard`
2026-03-11 Underestimate instead of overestimating segment length
2026-03-13 Wrap net ids in `NetId` type
2026-03-13 Move primitives to new file and add enum to group them together
2026-03-13 Place joints, segments, polygons in R-trees
2026-03-14 Add method to check if polygon contains point
2026-03-14 Toggle pin in pin selection upon click
2026-03-16 Bump `dearcut` version to 0.3.0
2026-03-17 Use `Vector2<i64>` instead of `[i64; 2]` in `navmesher.rs`
2026-03-19 Add methods to add multivertices to navmesher
2026-03-19 Do some renamings, some changes in `Cargo.toml`
2026-03-19 Rename `NavmesherBoard` to `Autorouter`, move it to own file
2026-03-20 Add separate methods to find all layer joints, segments, polygons
2026-05-16 Explain in comments how to point-in-polygon checking method works
2026-05-17 Split `Via` into input `ViaSpec` and actually stored `Via`
2026-05-18 Add (not yet used) private interface to modify joints without segment, via updates
2026-05-18 Add new type of compound, component
2026-05-19 Expand `board.rs` into a new module directory
2026-05-20 Add interfaces to move components
2026-05-23 Encapsulate layer indices in new `LayerId` type
2026-05-24 Load outlines to its own separate layer and group
2026-05-24 Get rid of layer groups. `LayerDesc`s already do the job
2026-05-25 Add missing code for vias
2026-05-26 Replace `RouteSelector` with `NetSelector`
    I don't think identifying routes by pin name pair is going to be really
    useful.
2026-05-27 Make containment mode dependent on left-to-right, right-to-left mouse drag
2026-05-27 Actually display the drag selection box, and some fixes
2026-05-28 Make it possible to select whole components. Use different color for pin selection
2026-05-29 Add capability to move components by dragging mouse
2026-06-02 Add (basic, WIP) methods to compute rect-overlaps of primitives
2026-06-02 Add methods to obtain pin and component attractions
2026-06-04 Add toggle button and slider to change step rate
2026-06-06 First crude attempt at autoplacing using simulated annealing
2026-06-07 Make it possible to hide debug overlay elements
